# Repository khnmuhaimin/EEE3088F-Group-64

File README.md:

# EEE3088F Micromouse Design Project

## Overview

This repository contains the design and implementation of the sensing and power subsystems for a micromouse project. The sensing subsystem is responsible for detecting walls and approximating distances to these walls using infrared (IR) sensors. The power subsystem is responsible for supplying power to the rest of the micromouse and controlling the motors used to move the micromouse around. This README provides an overview of the project.

## General Micromouse Features

- **Wall Detection**: Detects the presence of walls in three directions: forwards, left, and right.
- **PCB Design**: Includes the design of a custom PCB that integrates with the micromouse.
- **Autonomous Navigation**: Explores and solves a maze autonomously.

## Necessary Additional Components
- **STM32L476 microcontroller**
- **Motherboard PCB with PIN connections**
- **Wheels and motors for movement (multi-rotational drawing approximately 200mA each**
- **Battery LiPo 800mAh 3.7V**
- **Battery, Power and Sensing headers need to be purchased and soldered on during assembly**
- **5V Power supply for charging**
- **Device capable of running MATLAB**

## Installation

1. Clone the repository:

    ```
    git clone https://github.com/khnmuhaimin/EEE3088F-Group-64.git
    ```

2. Navigate to the project directory:

    ```
    cd EEE3088F-Group-64
    ```

3. Use KiCad to open up the project files for the custom PCB design.

## License

This project is licensed under the MIT License. See the `LICENSE` file for details.

## Contributors (Group 64)

- Luke Carter(CRTLUK001)
- Muhaimin Khan(KHNMUH063)

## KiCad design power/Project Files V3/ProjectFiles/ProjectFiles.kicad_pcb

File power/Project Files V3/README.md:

# Project Files
Power project files v3 which are the final files for the project

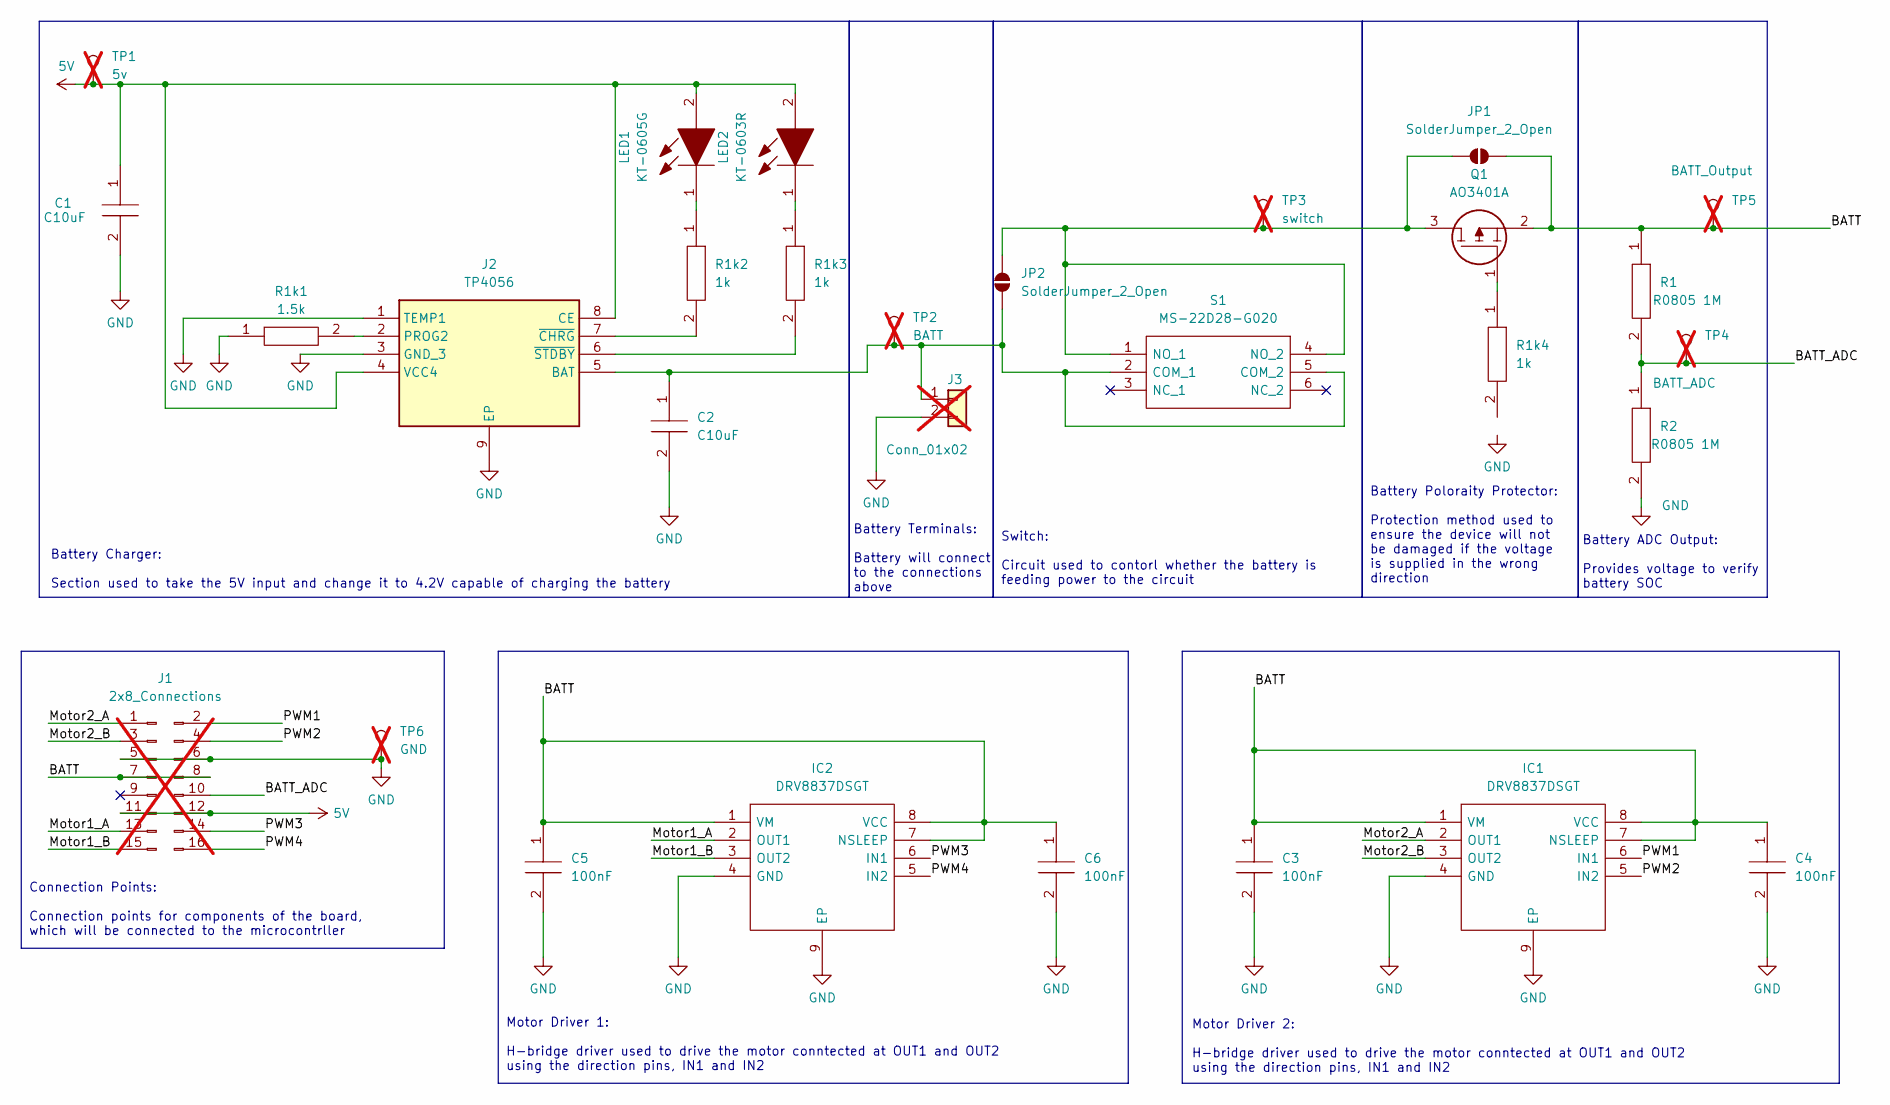
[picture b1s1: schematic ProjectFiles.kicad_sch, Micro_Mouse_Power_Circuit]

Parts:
C1, C2: C10uF; CAPC2012X145N
C3, C4, C5, C6: 100nF; CAPC1005X55N
IC1, IC2: DRV8837DSGT; SON50P200X200X80-9N
J1: 2x8_Connections; PinHeader_2x08_P2.54mm_Vertical; not fitted
J2: TP4056; SOIC127P600X175-9N; Manufacturer_Part_Number TP4056
J3: Conn_01x02; JST_PH_B2B-PH-K_1x02_P2.00mm_Vertical; not fitted
JP1, JP2: SolderJumper_2_Open; SolderJumper-2_P1.3mm_Open_RoundedPad1.0x1.5mm
LED1: KT-0605G; LEDC1608X70N
LED2: KT-0603R; LEDC1608X70N
Q1: AO3401A; SOT95P280X125-3N
R1, R2: R0805 1M; RESC2013X65N2
R1k1: 1.5k; RESC2013X65N
R1k2, R1k3, R1k4: 1k; RESC2013X65N
S1: MS-22D28-G020; MS22D28G020
TP1: 5v; TestPoint_Pad_D2.5mm; not fitted
TP2: BATT; TestPoint_Pad_D2.5mm; not fitted
TP3: switch; TestPoint_Pad_D2.5mm; not fitted
TP4: BATT_ADC; TestPoint_Pad_D2.5mm; not fitted
TP5: BATT_Output; TestPoint_Pad_D2.5mm; not fitted
TP6: GND; TestPoint_Pad_D2.5mm; not fitted

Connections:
5V: C1.1, J1.11, J1.12, J2.4 (VCC4), J2.8 (CE), LED1.2, LED2.2, TP1.1
/BATT: C3.1, C4.1, C5.1, C6.1, IC1.1 (VM), IC1.7 (NSLEEP), IC1.8 (VCC), IC2.1 (VM), IC2.7 (NSLEEP), IC2.8 (VCC), J1.7, J1.8, JP1.2 (B), Q1.2, R1.1, TP5.1
/BATT_ADC: J1.10, R1.2, R2.1, TP4.1
/Motor1_A: IC2.2 (OUT1), J1.13
/Motor1_B: IC2.3 (OUT2), J1.15
/Motor2_A: IC1.2 (OUT1), J1.1
/Motor2_B: IC1.3 (OUT2), J1.3
/PWM1: IC1.6 (IN1), J1.2
/PWM2: IC1.5 (IN2), J1.4
/PWM3: IC2.6 (IN1), J1.14
/PWM4: IC2.5 (IN2), J1.16
GND: C1.2, C2.2, C3.2, C4.2, C5.2, C6.2, IC1.4 (GND), IC1.9 (EP), IC2.4 (GND), IC2.9 (EP), J1.5, J1.6, J2.1 (TEMP1), J2.3 (GND_3), J2.9 (EP), J3.2, R1k1.1, R1k4.2, R2.2, TP6.1
unnamed: C2.1, J2.5 (BAT), J3.1, JP2.2 (B), S1.2 (COM_1), S1.5 (COM_2), TP2.1
unnamed: J2.2 (PROG2), R1k1.2
unnamed: J2.7 (~CHRG), R1k2.2
unnamed: J2.6 (~STDBY), R1k3.2
unnamed: JP1.1 (A), JP2.1 (A), Q1.3, S1.1 (NO_1), S1.4 (NO_2), TP3.1
unnamed: LED1.1, R1k2.1
unnamed: LED2.1, R1k3.1
unnamed: Q1.1, R1k4.1

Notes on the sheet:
Battery Terminals: Battery will connect to the connections above
Motor Driver 1: H-bridge driver used to drive the motor conntected at OUT1 and OUT2 using the direction pins, IN1 and IN2
Motor Driver 2: H-bridge driver used to drive the motor conntected at OUT1 and OUT2 using the direction pins, IN1 and IN2
Battery Charger: Section used to take the 5V input and change it to 4.2V capable of charging the battery
Connection Points: Connection points for components of the board, which will be connected to the microcontrller
Battery ADC Output: Provides voltage to verify battery SOC
Battery Poloraity Protector: Protection method used to ensure the device will not be damaged if the voltage is supplied in the wrong direction
Switch: Circuit used to contorl whether the battery is feeding power to the circuit

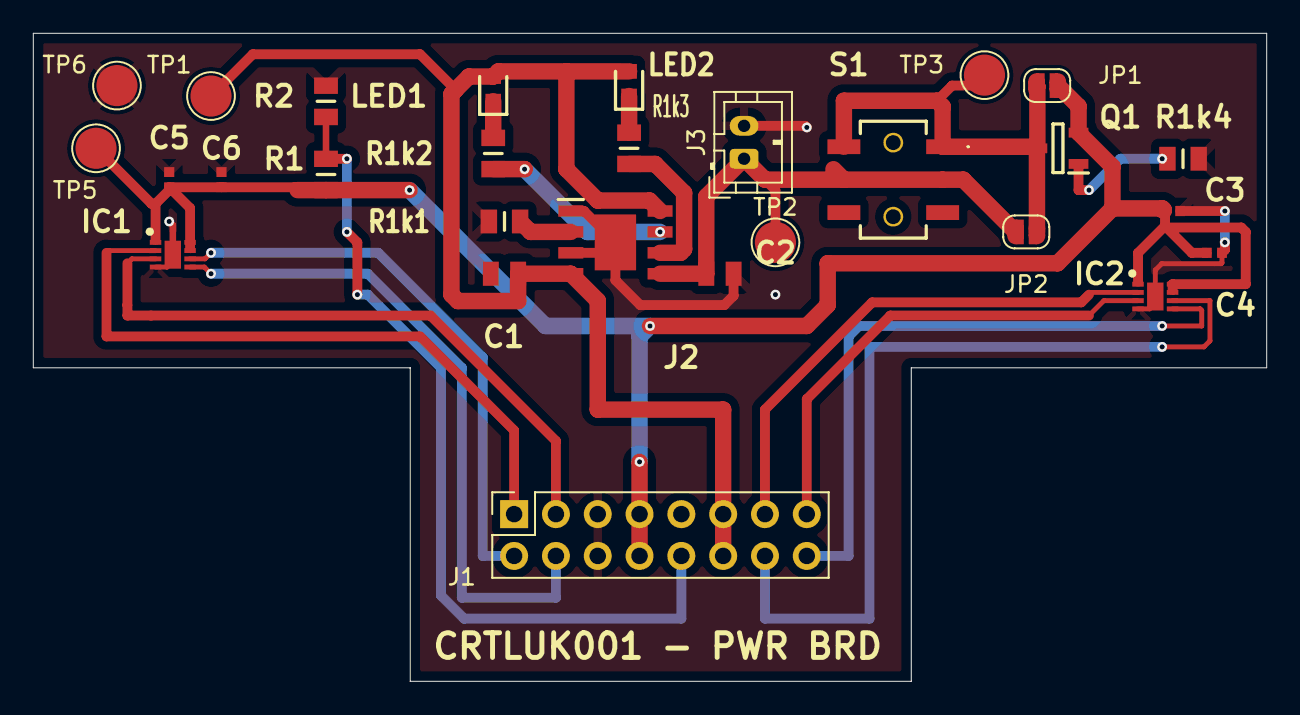
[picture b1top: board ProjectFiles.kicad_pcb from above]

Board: 2 copper layers, 74.9 x 39.4 mm, 28 parts (0 on the bottom side), 20 nets.

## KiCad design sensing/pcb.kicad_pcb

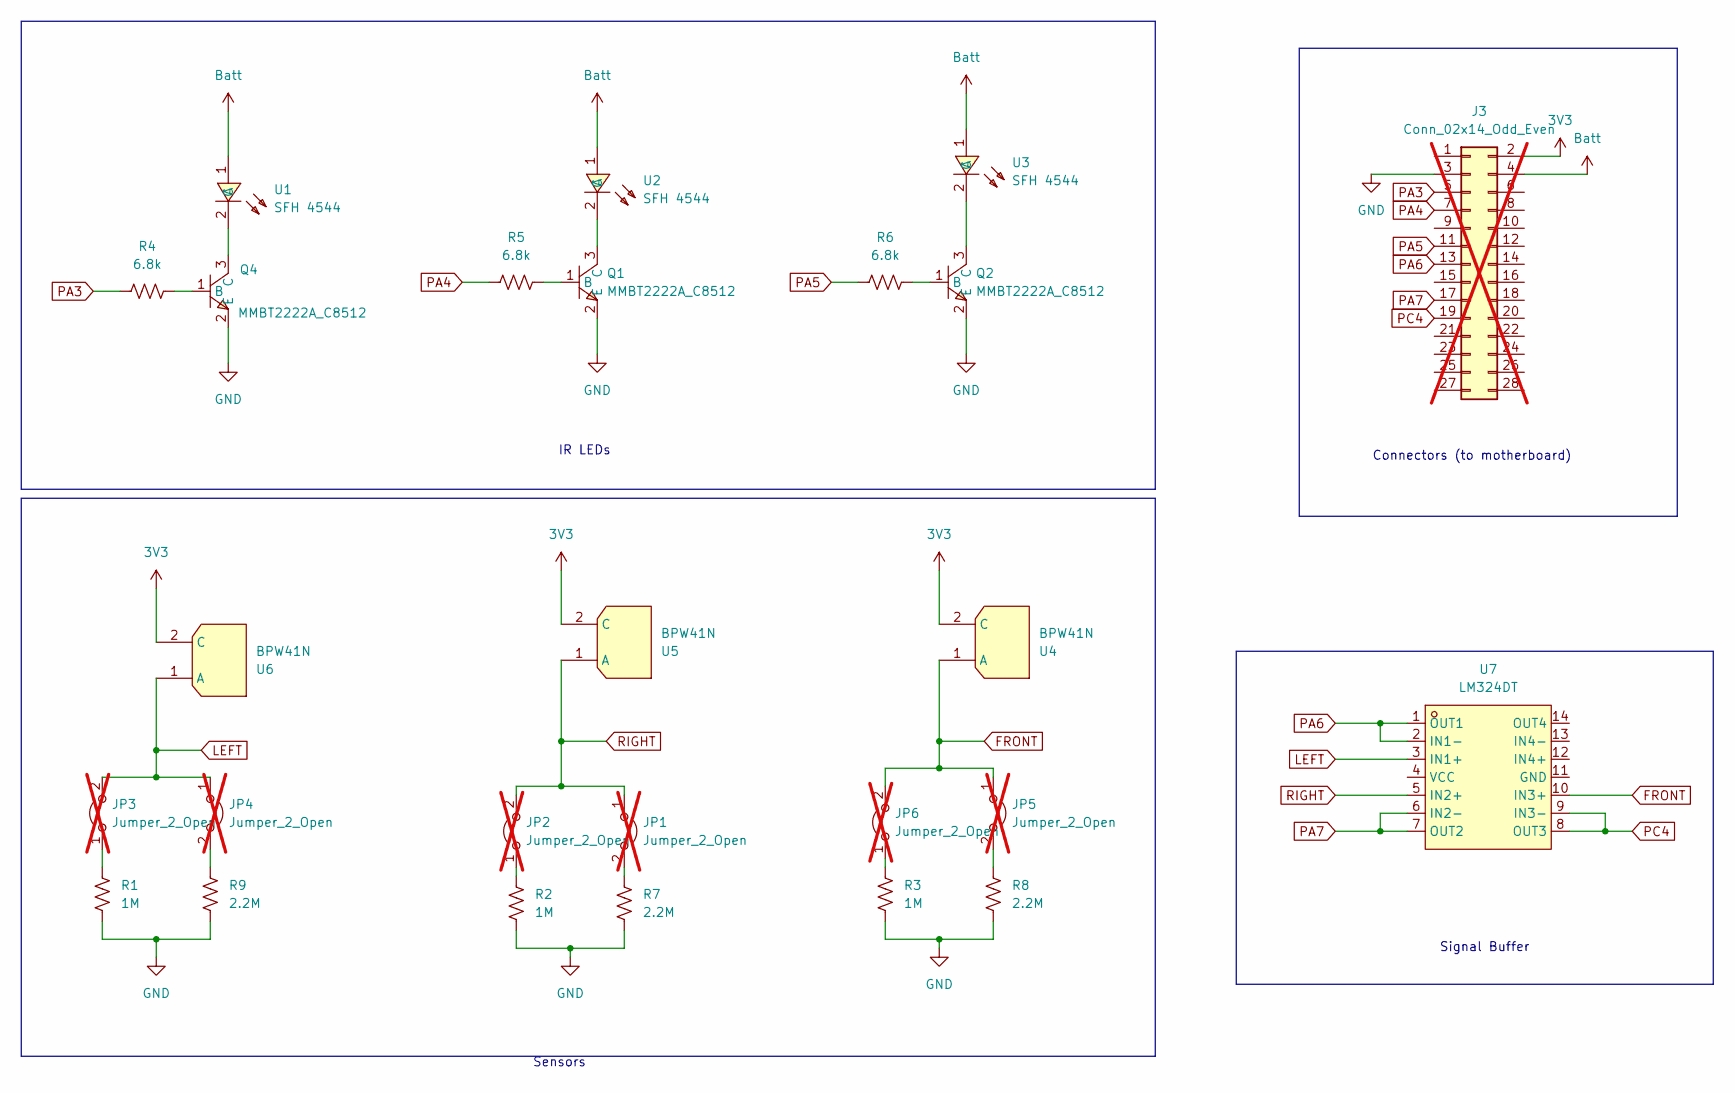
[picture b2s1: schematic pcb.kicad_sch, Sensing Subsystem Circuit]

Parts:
J3: Conn_02x14_Odd_Even; PinHeader_2x14_P2.54mm_Vertical; not fitted
JP1, JP2, JP3, JP4, JP5, JP6: Jumper_2_Open; SolderJumper-2_P1.3mm_Open_RoundedPad1.0x1.5mm; not fitted
Q1, Q2, Q4: MMBT2222A_C8512; SOT-23-3_L2.9-W1.3-P1.90-LS2.4-BR; LCSC Part C8512
R1, R2, R3: 1M; R_0805_2012Metric
R4, R5, R6: 6.8k; R_0805_2012Metric
R7, R8, R9: 2.2M; R_0805_2012Metric
U1, U2, U3: SFH 4544; LED_D5.0mm_Horizontal_O6.35mm_Z15.0mm; LCSC Part C2900370
U4, U5, U6: BPW41N; SENSOR-TH_BPW41N; LCSC Part C142586
U7: LM324DT; SOIC-14_L8.7-W3.9-P1.27-LS6.0-BL; LCSC Part C71035

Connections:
3V3: J3.2, U4.2 (C), U5.2 (C), U6.2 (C)
Batt: J3.4, U1.1 (A), U2.1 (A), U3.1 (A)
FRONT: JP5.1 (A), JP6.2 (B), U4.1 (A), U7.10 (IN3+)
GND: J3.3, Q1.2 (E), Q2.2 (E), Q4.2 (E), R1.2, R2.2, R3.2, R7.2, R8.2, R9.2
LEFT: JP3.2 (B), JP4.1 (A), U6.1 (A), U7.3 (IN1+)
unnamed: JP1.2 (B), R7.1
unnamed: JP2.1 (A), R2.1
unnamed: JP3.1 (A), R1.1
unnamed: JP4.2 (B), R9.1
unnamed: JP5.2 (B), R8.1
unnamed: JP6.1 (A), R3.1
unnamed: Q1.1 (B), R5.2
unnamed: Q1.3 (C), U2.2 (C)
unnamed: Q2.1 (B), R6.2
unnamed: Q2.3 (C), U3.2 (C)
unnamed: Q4.1 (B), R4.2
unnamed: Q4.3 (C), U1.2 (C)
PA3: J3.5, R4.1
PA4: J3.7, R5.1
PA5: J3.11, R6.1
PA6: J3.13, U7.1 (OUT1), U7.2 (IN1-)
PA7: J3.17, U7.6 (IN2-), U7.7 (OUT2)
PC4: J3.19, U7.8 (OUT3), U7.9 (IN3-)
RIGHT: JP1.1 (A), JP2.2 (B), U5.1 (A), U7.5 (IN2+)

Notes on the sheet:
Signal Buffer
Connectors (to motherboard)
Sensors
IR LEDs

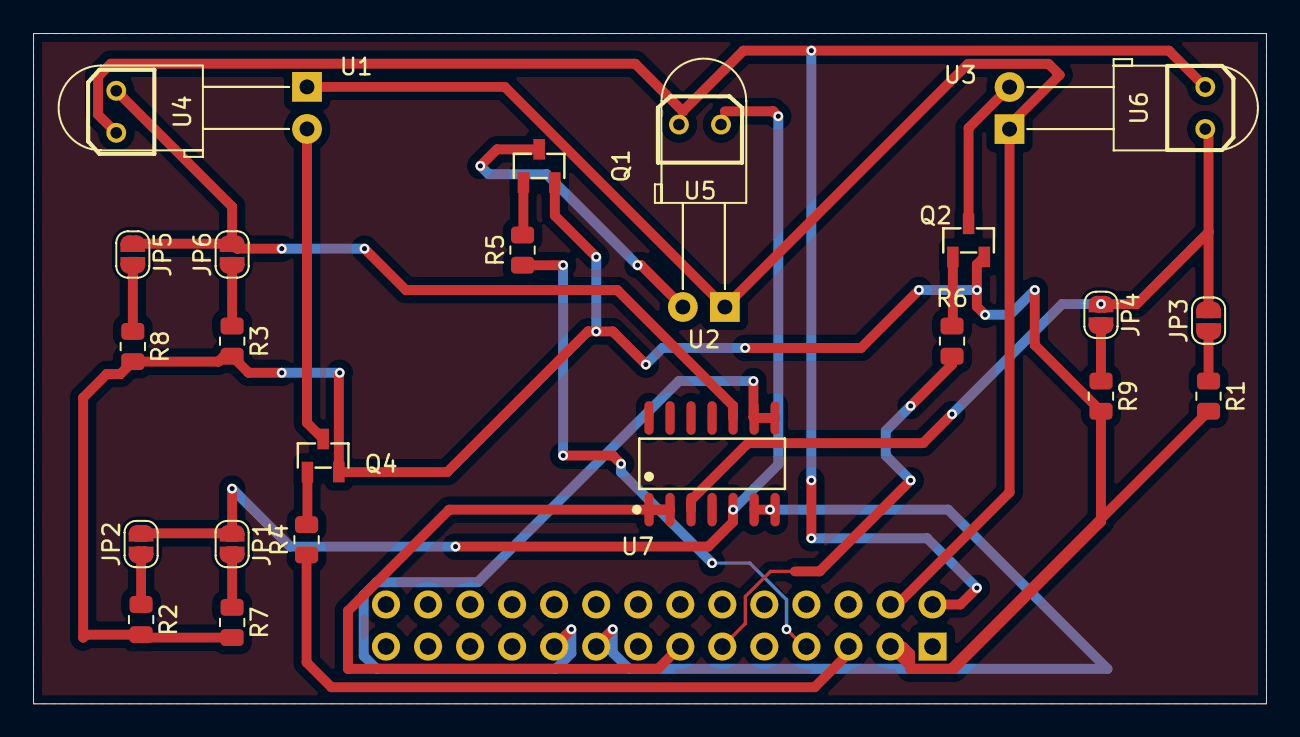
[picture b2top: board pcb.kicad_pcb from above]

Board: 2 copper layers, 74.5 x 40.5 mm, 26 parts (1 on the bottom side), 24 nets.

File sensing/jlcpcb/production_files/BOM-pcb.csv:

Comment,Designator,Footprint,LCSC
BPW41N,"U4,U5,U6",SENSOR-TH_BPW41N,C142586
SFH 4544,"U1,U2,U3",LED_D5.0mm_Horizontal_O6.35mm_Z15.0mm,C2900370
LM324DT,U7,SOIC-14_L8.7-W3.9-P1.27-LS6.0-BL,C71035
MMBT2222A_C8512,"Q1,Q2,Q4",SOT-23-3_L2.9-W1.3-P1.90-LS2.4-BR,C8512
1M,R1,R_0805_2012Metric,
2.2M,R7,R_0805_2012Metric,
2.2M,R9,R_0805_2012Metric,
6.8k,R6,R_0805_2012Metric,
1M,R2,R_0805_2012Metric,
6.8k,R4,R_0805_2012Metric,
6.8k,R5,R_0805_2012Metric,
1M,R3,R_0805_2012Metric,
2.2M,R8,R_0805_2012Metric,

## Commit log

2024-03-13 Initial commit for README.md
2024-03-13 Initial commit for .gitignore
2024-03-13 Created blank sensor schematics
2024-03-16 Created schematic for v0 of sensing subsystem
2024-03-16 Updated README with notes (mainly to myself)
2024-03-24 Project Files added
2024-04-21 Delete sensor directory
    To upload new schematics
2024-04-21 Added final design for sensing subsystem
2024-04-21 Rename License.txt to LICENSE
2024-04-21 Uploaded most recent kicad files and design images
2024-04-21 Project Description
2024-04-21 Backup Files uploaded
2024-04-21 Uploaded files to correct location
